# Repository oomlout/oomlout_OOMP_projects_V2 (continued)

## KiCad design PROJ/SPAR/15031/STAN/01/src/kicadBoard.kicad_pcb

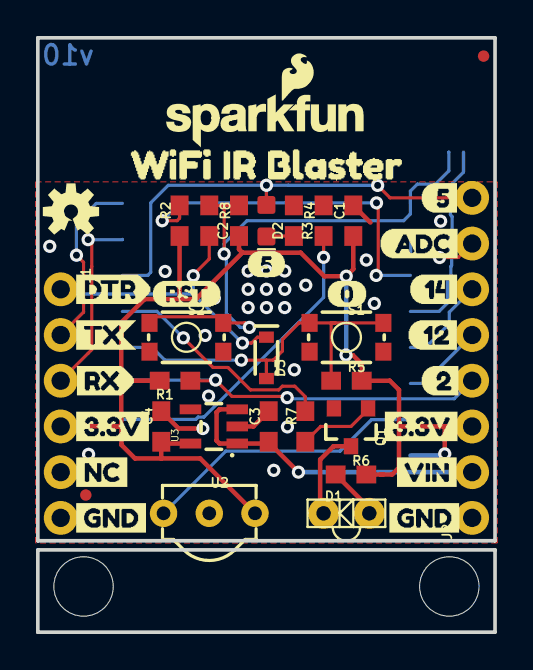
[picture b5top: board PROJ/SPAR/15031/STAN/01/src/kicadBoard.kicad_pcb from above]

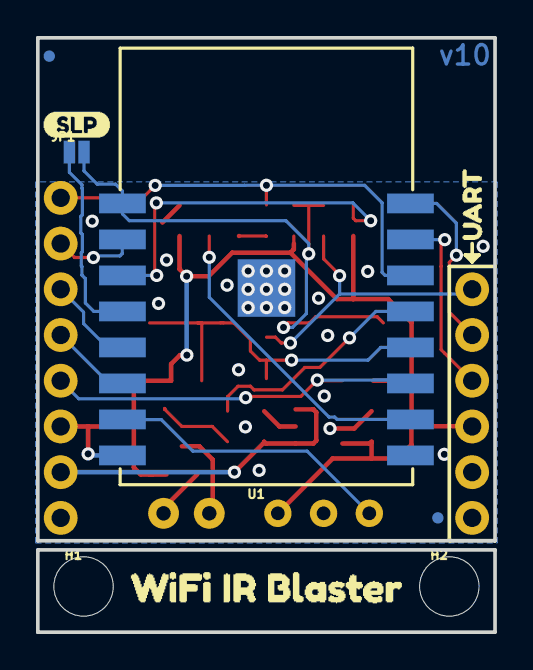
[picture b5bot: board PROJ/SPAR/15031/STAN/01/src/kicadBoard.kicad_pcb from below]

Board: 2 copper layers, 25.4 x 33.0 mm, 55 parts (9 on the bottom side), 22 nets.

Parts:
C1, C2, C3: 1.0uF; 0603
C4: 2.2uF; 0603
D1: IR-LED; LTE-302
D2: GREEN; LED-0603
D3: 250mA/100V; SOD-323
FD1, FD2, FD3, FD4: FIDUCIALUFIDUCIAL; FIDUCIAL-MICRO
FRAME1: FRAME-LETTER; CREATIVE_COMMONS
H1, H2: STAND-OFF
J1: 1X06_NO_SILK
J2: 1X08_NO_SILK
JP1: Deep-Sleep; SMT-JUMPER_2_NO_NO-SILK
LOGO1: OSHW-LOGOS; OSHW-LOGO-S
LOGO2: SFE_LOGO_NAME_FLAME.1_INCH; SFE_LOGO_NAME_FLAME_.1
LOGO3: REVISION
Q1: 600mA/40V; SOT23-3
R1, R2, R4, R8: 10k; 0603
R3, R5, R7: 1k; 0603
R6: 20; 0603
S1: GPIO0; TACTILE_SWITCH_SMD_4.6X2.8MM
S2: RESET; TACTILE_SWITCH_SMD_4.6X2.8MM
U1: ESP-12S
U2: 38kHz; TSOP382
U3: 3.3V; SOT23-5
U$1: 512
U$2, U$21: 3#3V4
U$3: SLP14
U$4, U$13: WIFI_IR_BLASTER11
U$5: UART0
U$6: DTR1
U$7: NC0
U$8: 511
U$9: ADC10
U$10: 129
U$11: 148
U$12: 27
U$14: 013
U$15: RST14
U$19: TX2
U$20: RX3
U$22, U$24: GND5
U$23: VIN6

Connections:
3.3V: C1.1, C4.1, J1.4, J2.3, R1.2, R2.1, R5.2, R6.2, R8.1, U1.8, U2.3, U3.5
ADC: J2.7, U1.2
CHIP_EN: R2.2, U1.3
DTR: C2.2, D3.C, J1.1
GND: C1.2, C3.2, C4.2, J1.6, J2.1, Q1.2, R3.1, R4.2, S1.1, S1.2, S2.1, S2.2, U1.9, U1.P$1, U2.2, U3.2
IO0: D3.A, R5.1, S1.3, S1.4, U1.12
IO2: J2.4, R1.1, U1.11
IO5: D2.A, J2.8, U1.14
IO12: J2.5, U1.6
IO14: J2.6, U1.5
IO15: R4.1, U1.10
IO16: JP1.1, U1.4
IR_IN: U1.7, U2.1
IR_OUT: R7.2, U1.13
unnamed: D2.C, R3.2
unnamed: D1.C, Q1.3
unnamed: D1.A, R6.1
unnamed: Q1.1, R7.1
RESET: C2.1, JP1.2, R8.2, S2.3, S2.4, U1.1
RXI: J1.3, U1.15
TXO: J1.2, U1.16
VIN: C3.1, J2.2, U3.1, U3.3

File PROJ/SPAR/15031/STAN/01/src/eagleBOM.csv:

"Part";"Value";"Device";"Package";"Description";"PROD_ID";"SF_ID";"VALUE";
"C1";"1.0uF";"1.0UF-0603-16V-10%";"0603";"1µF ceramic capacitors";"CAP-00868";"";"1.0uF";
"C2";"1.0uF";"1.0UF-0603-16V-10%";"0603";"1µF ceramic capacitors";"CAP-00868";"";"1.0uF";
"C3";"1.0uF";"1.0UF-0603-16V-10%";"0603";"1µF ceramic capacitors";"CAP-00868";"";"1.0uF";
"C4";"2.2uF";"2.2UF-0603-10V-20%";"0603";"2.2µF ceramic capacitors";"CAP-07888";"";"2.2uF";
"D1";"IR-LED";"LED-IRSIDE_EMITTER";"LTE-302";"Infrared LED (IR)";"DIO-10904";"SEN-00241";"";
"D2";"GREEN";"LED-GREEN0603";"LED-0603";"Green SMD LED";"DIO-00821";"";"GREEN";
"D3";"250mA/100V";"DIODE-BAS16J";"SOD-323";"Diode";"DIO-09646";"";"250mA/100V";
"FD1";"FIDUCIALUFIDUCIAL";"FIDUCIALUFIDUCIAL";"FIDUCIAL-MICRO";"Fiducial Alignment Points";"";"";"";
"FD2";"FIDUCIALUFIDUCIAL";"FIDUCIALUFIDUCIAL";"FIDUCIAL-MICRO";"Fiducial Alignment Points";"";"";"";
"FD3";"FIDUCIALUFIDUCIAL";"FIDUCIALUFIDUCIAL";"FIDUCIAL-MICRO";"Fiducial Alignment Points";"";"";"";
"FD4";"FIDUCIALUFIDUCIAL";"FIDUCIALUFIDUCIAL";"FIDUCIAL-MICRO";"Fiducial Alignment Points";"";"";"";
"FRAME1";"FRAME-LETTER";"FRAME-LETTER";"CREATIVE_COMMONS";"Schematic Frame - Letter";"";"";"";
"H1";"STAND-OFF";"STAND-OFF";"STAND-OFF";"Stand Off";"";"";"";
"H2";"STAND-OFF";"STAND-OFF";"STAND-OFF";"Stand Off";"";"";"";
"J1";"";"6_PIN_SERIAL_TARGETNO_SILK";"1X06_NO_SILK";"6-pin header connection for use with the "FTDI BASIC" pinout - TARGET SIDE.";"";"";"";
"J2";"";"CONN_08NO_SILK_FEMALE_PTH";"1X08_NO_SILK";"Multi connection point. Often used as Generic Header-pin footprint for 0.1 inch spaced/style header connections";"CONN-08438";"";"";
"JP1";"Deep-Sleep";"JUMPER-SMT_2_NO_NO-SILK";"SMT-JUMPER_2_NO_NO-SILK";"Normally open jumper";"";"";"";
"LOGO1";"OSHW-LOGOS";"OSHW-LOGOS";"OSHW-LOGO-S";"Open-Source Hardware (OSHW) Logo";"";"";"";
"LOGO2";"SFE_LOGO_NAME_FLAME.1_INCH";"SFE_LOGO_NAME_FLAME.1_INCH";"SFE_LOGO_NAME_FLAME_.1";"SparkFun Font Logo w/ Flame";"";"";"";
"LOGO3";"REVISION";"REVISION";"REVISION";""Revision By" Text";"";"";"";
"Q1";"600mA/40V";"TRANS_NPN-MMBT2222AL";"SOT23-3";"NPN transistor";"TRANS-08049";"";"600mA/40V";
"R1";"10k";"10KOHM-0603-1/10W-1%";"0603";"10kΩ resistor";"RES-00824";"";"10k";
"R2";"10k";"10KOHM-0603-1/10W-1%";"0603";"10kΩ resistor";"RES-00824";"";"10k";
"R3";"1k";"1KOHM-0603-1/10W-1%";"0603";"1kΩ resistor";"RES-07856";"";"1k";
"R4";"10k";"10KOHM-0603-1/10W-1%";"0603";"10kΩ resistor";"RES-00824";"";"10k";
"R5";"1k";"1KOHM-0603-1/10W-1%";"0603";"1kΩ resistor";"RES-07856";"";"1k";
"R6";"20";"20OHM-0603-1/10W-1%";"0603";"RES-07862";"RES-07862";"";"20";
"R7";"1k";"1KOHM-0603-1/10W-1%";"0603";"1kΩ resistor";"RES-07856";"";"1k";
"R8";"10k";"10KOHM-0603-1/10W-1%";"0603";"10kΩ resistor";"RES-00824";"";"10k";
"S1";"GPIO0";"MOMENTARY-SWITCH-SPST-SMD-4.6X2.8MM";"TACTILE_SWITCH_SMD_4.6X2.8MM";"Momentary Switch (Pushbutton) - SPST";"SWCH-13065";"";"";
"S2";"RESET";"MOMENTARY-SWITCH-SPST-SMD-4.6X2.8MM";"TACTILE_SWITCH_SMD_4.6X2.8MM";"Momentary Switch (Pushbutton) - SPST";"SWCH-13065";"";"";
"U1";"ESP-12S";"ESP-12S";"ESP-12S";"AI-Thinker ESP-12S";"IC-14115";"";"";
"U2";"38kHz";"TSOP38238";"TSOP382";"Vishay Semiconductor TSOP32838 - 38kHz IR Receiver";"SEN-14114";"";"38kHz";
"U3";"3.3V";"V_REG_AP2112K-3.3V";"SOT23-5";"AP2112 - 600mA CMOS LDO Regulator w/ Enable";"VREG-12457";"";"3.3V";

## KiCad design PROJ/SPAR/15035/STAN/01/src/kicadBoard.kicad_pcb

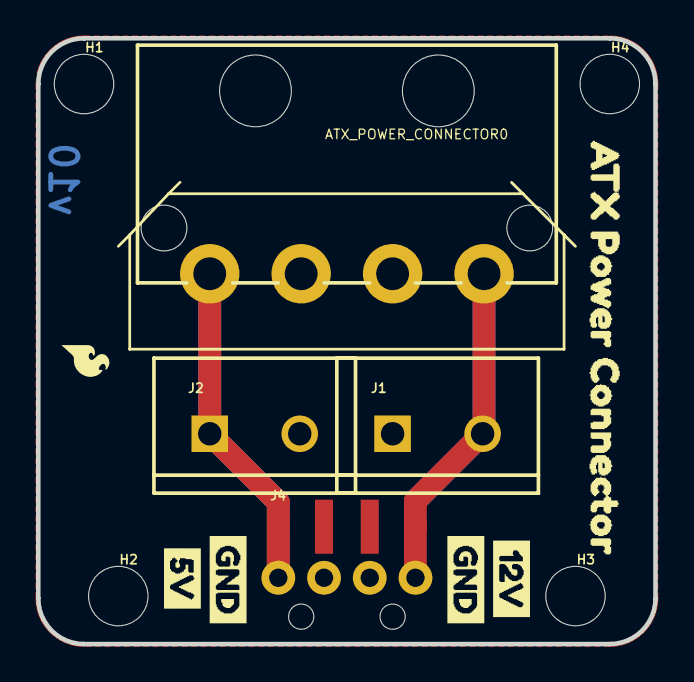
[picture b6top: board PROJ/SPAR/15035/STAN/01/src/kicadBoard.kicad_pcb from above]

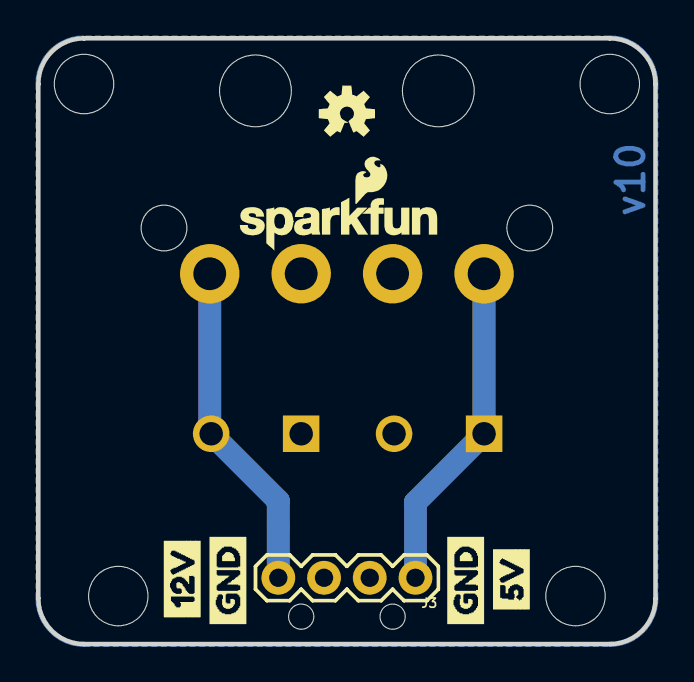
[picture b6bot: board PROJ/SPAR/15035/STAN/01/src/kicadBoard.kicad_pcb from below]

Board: 2 copper layers, 34.3 x 33.7 mm, 22 parts (7 on the bottom side), 3 nets.

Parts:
ATX_POWER_CONNECTOR0: COMPUTER_PERIPHERAL_POWERRA-VT; COMPUTER-PERIPHERAL-POWER-RA-VT
FRAME1: FRAME-LETTER; CREATIVE_COMMONS
H1, H2, H3, H4: STAND-OFF
J1, J2: SCREWTERMINAL-5MM-2
J3: 1X04
J4: 1X04_SMD_RA_MALE
LOGO1: OSHW-LOGOS; OSHW-LOGO-S
LOGO2: SFE_LOGO_NAME_FLAME.1_INCH; SFE_LOGO_NAME_FLAME_.1
LOGO3: SFE_LOGO_FLAME.1_INCH; SFE_LOGO_FLAME_.1
U$1, U$5: 12V0
U$2, U$8: 5V0
U$3, U$4, U$6, U$7: GND0
U$9: ATX_POWER_CONNECTOR0

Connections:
5V: ATX_POWER_CONNECTOR0.5V, J2.1, J3.1, J4.1
12V: ATX_POWER_CONNECTOR0.12V, J1.2, J3.4, J4.4
GND: ATX_POWER_CONNECTOR0.GND@1, ATX_POWER_CONNECTOR0.GND@2, J1.1, J2.2, J3.2, J3.3, J4.2, J4.3

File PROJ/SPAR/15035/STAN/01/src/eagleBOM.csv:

"Part";"Value";"Device";"Package";"Description";"PROD_ID";"SF_ID";"SF_SKU";
"ATX_POWER_CONNECTOR";"COMPUTER_PERIPHERAL_POWERRA-VT";"COMPUTER_PERIPHERAL_POWERRA-VT";"COMPUTER-PERIPHERAL-POWER-RA-VT";"ATX 4-Pin Power Supply Connector - Right Angle and Vertical PTH Mount";"PRT-15700";"";"";
"FRAME1";"FRAME-LETTER";"FRAME-LETTER";"CREATIVE_COMMONS";"Schematic Frame - Letter";"";"";"";
"H1";"STAND-OFF";"STAND-OFF";"STAND-OFF";"Stand Off";"";"";"";
"H2";"STAND-OFF";"STAND-OFF";"STAND-OFF";"Stand Off";"";"";"";
"H3";"STAND-OFF";"STAND-OFF";"STAND-OFF";"Stand Off";"";"";"";
"H4";"STAND-OFF";"STAND-OFF";"STAND-OFF";"Stand Off";"";"";"";
"J1";"";"CONN_025MM";"SCREWTERMINAL-5MM-2";"Multi connection point. Often used as Generic Header-pin footprint for 0.1 inch spaced/style header connections";"";"";"PRT-08432";
"J2";"";"CONN_025MM";"SCREWTERMINAL-5MM-2";"Multi connection point. Often used as Generic Header-pin footprint for 0.1 inch spaced/style header connections";"";"";"PRT-08432";
"J3";"";"CONN_04";"1X04";"Multi connection point. Often used as Generic Header-pin footprint for 0.1 inch spaced/style header connections";"CONN-09696";"";"";
"J4";"";"CONN_04SMD";"1X04_SMD_RA_MALE";"Multi connection point. Often used as Generic Header-pin footprint for 0.1 inch spaced/style header connections";"CONN-09140";"PRT-12638";"";
"LOGO1";"OSHW-LOGOS";"OSHW-LOGOS";"OSHW-LOGO-S";"Open-Source Hardware (OSHW) Logo";"";"";"";
"LOGO2";"SFE_LOGO_NAME_FLAME.1_INCH";"SFE_LOGO_NAME_FLAME.1_INCH";"SFE_LOGO_NAME_FLAME_.1";"SparkFun Font Logo w/ Flame";"";"";"";
"LOGO3";"SFE_LOGO_FLAME.1_INCH";"SFE_LOGO_FLAME.1_INCH";"SFE_LOGO_FLAME_.1";"SparkFun Flame Logo";"";"";"";

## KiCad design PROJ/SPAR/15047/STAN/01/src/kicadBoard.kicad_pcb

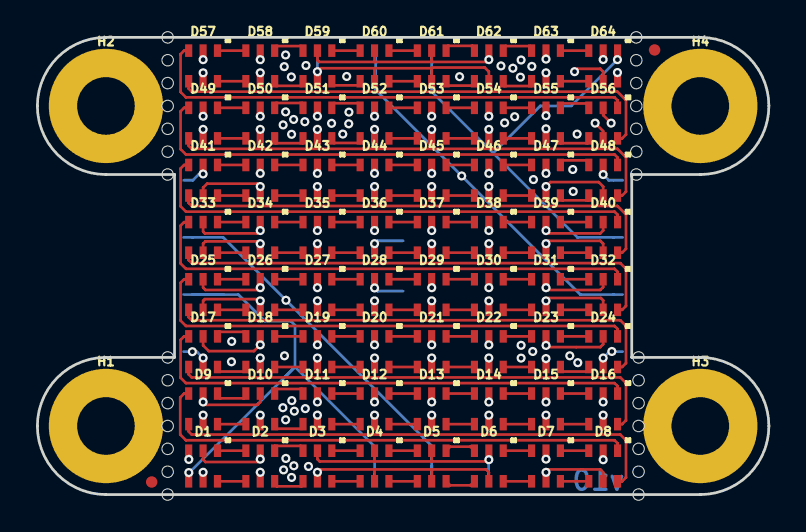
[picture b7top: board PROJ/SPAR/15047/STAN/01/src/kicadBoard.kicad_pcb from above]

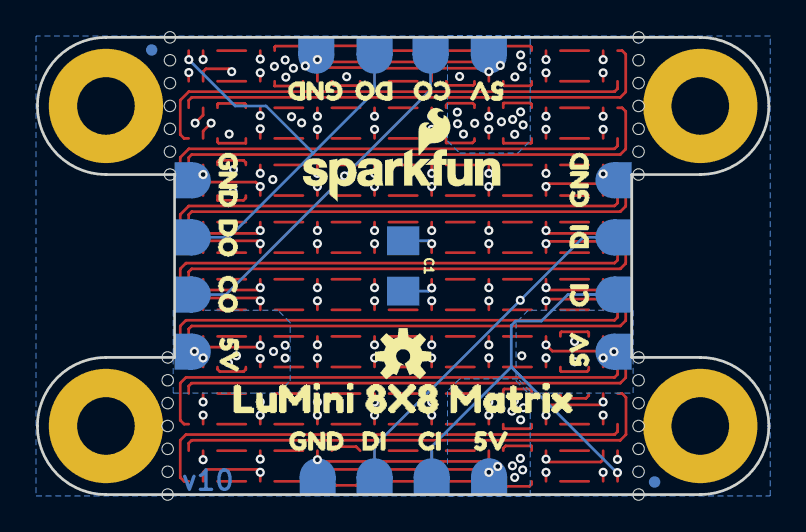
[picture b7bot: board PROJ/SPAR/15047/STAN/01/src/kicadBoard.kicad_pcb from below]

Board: 4 copper layers, 40.6 x 25.4 mm, 138 parts (38 on the bottom side), 132 nets.

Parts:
@HOLE0, @HOLE1, @HOLE2, @HOLE3, @HOLE4, @HOLE5, @HOLE6, @HOLE7, @HOLE8, @HOLE9, @HOLE10, @HOLE11, @HOLE12, @HOLE13, @HOLE14, @HOLE15, @HOLE16, @HOLE17, @HOLE18, @HOLE19, @HOLE20, @HOLE21, @HOLE22, @HOLE23, @HOLE24, @HOLE25, @HOLE26, @HOLE27: (no value)
C1: DNP; 1206
D1, D2, D3, D4, D5, D6, D7, D8, D9, D10, D11, D12, D13, D14, D15, D16, D17, D18, D19, D20, D21, D22, D23, D24, D25, D26, D27, D28, D29, D30, D31, D32, D33, D34, D35, D36, D37, D38, D39, D40, D41, D42, D43, D44, D45, D46, D47, D48, D49, D50, D51, D52, D53, D54, D55, D56, D57, D58, D59, D60, D61, D62, D63, D64: APA102-2020
FD1, FD2, FD3, FD4: FIDUCIALUFIDUCIAL; FIDUCIAL-MICRO
FRAME1: FRAME-LEDGER; CREATIVE_COMMONS
H1, H2, H3, H4: STANDOFF_ELECTRICAL-NOTHERMALS; STANDOFF-ELECTRICAL-NOTHERMALS
J1, J2, J3, J4, J5, J6, J7, J8, J9, J10, J11, J12, J13, J14, J15, J16: LED_PAD; CIRCULARPAD
LOGO1: SFE_LOGO_NAME_FLAME.1_INCH; SFE_LOGO_NAME_FLAME_.1
LOGO2: OSHW-LOGOS; OSHW-LOGO-S
U$1, U$2, U$11, U$18: 5V5
U$3, U$12: CI1
U$4, U$17: CO3
U$5, U$13: DI2
U$6, U$16: DO4
U$7, U$8, U$14, U$15: GND6
U$9: LUMINI_8X8_MATRIX0
U$10: ORDERING_INSTRUCTIONS

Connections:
5V: C1.1, D1.VDD, D2.VDD, D3.VDD, D4.VDD, D5.VDD, D6.VDD, D7.VDD, D8.VDD, D9.VDD, D10.VDD, D11.VDD, D12.VDD, D13.VDD, D14.VDD, D15.VDD, D16.VDD, D17.VDD, D18.VDD, D19.VDD, D20.VDD, D21.VDD, D22.VDD, D23.VDD, D24.VDD, D25.VDD, D26.VDD, D27.VDD, D28.VDD, D29.VDD, D30.VDD, D31.VDD, D32.VDD, D33.VDD, D34.VDD, D35.VDD, D36.VDD, D37.VDD, D38.VDD, D39.VDD, D40.VDD, D41.VDD, D42.VDD, D43.VDD, D44.VDD, D45.VDD, D46.VDD, D47.VDD, D48.VDD, D49.VDD, D50.VDD, D51.VDD, D52.VDD, D53.VDD, D54.VDD, D55.VDD, D56.VDD, D57.VDD, D58.VDD, D59.VDD, D60.VDD, D61.VDD, D62.VDD, D63.VDD, D64.VDD, J1.P$1, J1.P$2, J2.P$1, J2.P$2, J5.P$1, J5.P$2, J8.P$1, J8.P$2
CI: D1.CKI, J9.P$1, J9.P$2, J10.P$1, J10.P$2
CO: D64.CKO, J13.P$1, J13.P$2, J14.P$1, J14.P$2
CT1: D9.CKO, D10.CKI
CT2: D18.CKO, D19.CKI
CT3: D27.CKO, D28.CKI
CT4: D36.CKO, D37.CKI
CT5: D45.CKO, D46.CKI
CT6: D54.CKO, D55.CKI
CT7: D63.CKO, D64.CKI
DI: D1.SDI, J11.P$1, J11.P$2, J12.P$1, J12.P$2
DO: D64.SDO, J15.P$1, J15.P$2, J16.P$1, J16.P$2
DT1: D9.SDO, D10.SDI
DT2: D18.SDO, D19.SDI
DT3: D27.SDO, D28.SDI
DT4: D36.SDO, D37.SDI
DT5: D45.SDO, D46.SDI
DT6: D54.SDO, D55.SDI
DT7: D63.SDO, D64.SDI
GND: C1.2, D1.GND, D2.GND, D3.GND, D4.GND, D5.GND, D6.GND, D7.GND, D8.GND, D9.GND, D10.GND, D11.GND, D12.GND, D13.GND, D14.GND, D15.GND, D16.GND, D17.GND, D18.GND, D19.GND, D20.GND, D21.GND, D22.GND, D23.GND, D24.GND, D25.GND, D26.GND, D27.GND, D28.GND, D29.GND, D30.GND, D31.GND, D32.GND, D33.GND, D34.GND, D35.GND, D36.GND, D37.GND, D38.GND, D39.GND, D40.GND, D41.GND, D42.GND, D43.GND, D44.GND, D45.GND, D46.GND, D47.GND, D48.GND, D49.GND, D50.GND, D51.GND, D52.GND, D53.GND, D54.GND, D55.GND, D56.GND, D57.GND, D58.GND, D59.GND, D60.GND, D61.GND, D62.GND, D63.GND, D64.GND, H1.P1, H2.P1, H3.P1, H4.P1, J3.P$1, J3.P$2, J4.P$1, J4.P$2, J6.P$1, J6.P$2, J7.P$1, J7.P$2
unnamed: D1.SDO, D2.SDI
unnamed: D1.CKO, D2.CKI
unnamed: D2.SDO, D3.SDI
unnamed: D2.CKO, D3.CKI
unnamed: D3.SDO, D4.SDI
unnamed: D3.CKO, D4.CKI
unnamed: D4.SDO, D5.SDI
unnamed: D4.CKO, D5.CKI
unnamed: D5.SDO, D6.SDI
unnamed: D5.CKO, D6.CKI
unnamed: D6.SDO, D7.SDI
unnamed: D6.CKO, D7.CKI
unnamed: D7.SDO, D8.SDI
unnamed: D7.CKO, D8.CKI
unnamed: D8.SDO, D9.SDI
unnamed: D8.CKO, D9.CKI
unnamed: D10.SDO, D11.SDI
unnamed: D10.CKO, D11.CKI
unnamed: D11.SDO, D12.SDI
unnamed: D11.CKO, D12.CKI
unnamed: D12.SDO, D13.SDI
unnamed: D12.CKO, D13.CKI
unnamed: D13.SDO, D14.SDI
unnamed: D13.CKO, D14.CKI
unnamed: D14.SDO, D15.SDI
unnamed: D14.CKO, D15.CKI
unnamed: D15.SDO, D16.SDI
unnamed: D15.CKO, D16.CKI
unnamed: D16.SDO, D17.SDI
unnamed: D16.CKO, D17.CKI
unnamed: D17.SDO, D18.SDI
unnamed: D17.CKO, D18.CKI
unnamed: D19.SDO, D20.SDI
unnamed: D19.CKO, D20.CKI
unnamed: D20.SDO, D21.SDI
unnamed: D20.CKO, D21.CKI
unnamed: D21.SDO, D22.SDI
unnamed: D21.CKO, D22.CKI
unnamed: D22.SDO, D23.SDI
unnamed: D22.CKO, D23.CKI
unnamed: D23.SDO, D24.SDI
unnamed: D23.CKO, D24.CKI
unnamed: D24.SDO, D25.SDI
unnamed: D24.CKO, D25.CKI
unnamed: D25.SDO, D26.SDI
unnamed: D25.CKO, D26.CKI
unnamed: D26.SDO, D27.SDI
unnamed: D26.CKO, D27.CKI
unnamed: D28.SDO, D29.SDI
unnamed: D28.CKO, D29.CKI
unnamed: D29.SDO, D30.SDI
unnamed: D29.CKO, D30.CKI
unnamed: D30.SDO, D31.SDI
unnamed: D30.CKO, D31.CKI
unnamed: D31.SDO, D32.SDI
unnamed: D31.CKO, D32.CKI
unnamed: D32.SDO, D33.SDI
unnamed: D32.CKO, D33.CKI
unnamed: D33.SDO, D34.SDI
unnamed: D33.CKO, D34.CKI
unnamed: D34.SDO, D35.SDI
unnamed: D34.CKO, D35.CKI
unnamed: D35.SDO, D36.SDI
unnamed: D35.CKO, D36.CKI
unnamed: D37.SDO, D38.SDI
unnamed: D37.CKO, D38.CKI
unnamed: D38.SDO, D39.SDI
unnamed: D38.CKO, D39.CKI
unnamed: D39.SDO, D40.SDI
unnamed: D39.CKO, D40.CKI
unnamed: D40.SDO, D41.SDI
unnamed: D40.CKO, D41.CKI
unnamed: D41.SDO, D42.SDI
unnamed: D41.CKO, D42.CKI
unnamed: D42.SDO, D43.SDI
unnamed: D42.CKO, D43.CKI
unnamed: D43.SDO, D44.SDI
unnamed: D43.CKO, D44.CKI
unnamed: D44.SDO, D45.SDI
unnamed: D44.CKO, D45.CKI
unnamed: D46.SDO, D47.SDI
unnamed: D46.CKO, D47.CKI
unnamed: D47.SDO, D48.SDI
unnamed: D47.CKO, D48.CKI
unnamed: D48.SDO, D49.SDI
unnamed: D48.CKO, D49.CKI
unnamed: D49.SDO, D50.SDI
unnamed: D49.CKO, D50.CKI
unnamed: D50.SDO, D51.SDI
unnamed: D50.CKO, D51.CKI
unnamed: D51.SDO, D52.SDI
unnamed: D51.CKO, D52.CKI
unnamed: D52.SDO, D53.SDI
unnamed: D52.CKO, D53.CKI
unnamed: D53.SDO, D54.SDI
unnamed: D53.CKO, D54.CKI
unnamed: D55.SDO, D56.SDI
unnamed: D55.CKO, D56.CKI
unnamed: D56.SDO, D57.SDI
unnamed: D56.CKO, D57.CKI
unnamed: D57.SDO, D58.SDI
unnamed: D57.CKO, D58.CKI
unnamed: D58.SDO, D59.SDI
unnamed: D58.CKO, D59.CKI
unnamed: D59.SDO, D60.SDI
unnamed: D59.CKO, D60.CKI
unnamed: D60.SDO, D61.SDI
unnamed: D60.CKO, D61.CKI
unnamed: D61.SDO, D62.SDI
unnamed: D61.CKO, D62.CKI
unnamed: D62.SDO, D63.SDI
unnamed: D62.CKO, D63.CKI

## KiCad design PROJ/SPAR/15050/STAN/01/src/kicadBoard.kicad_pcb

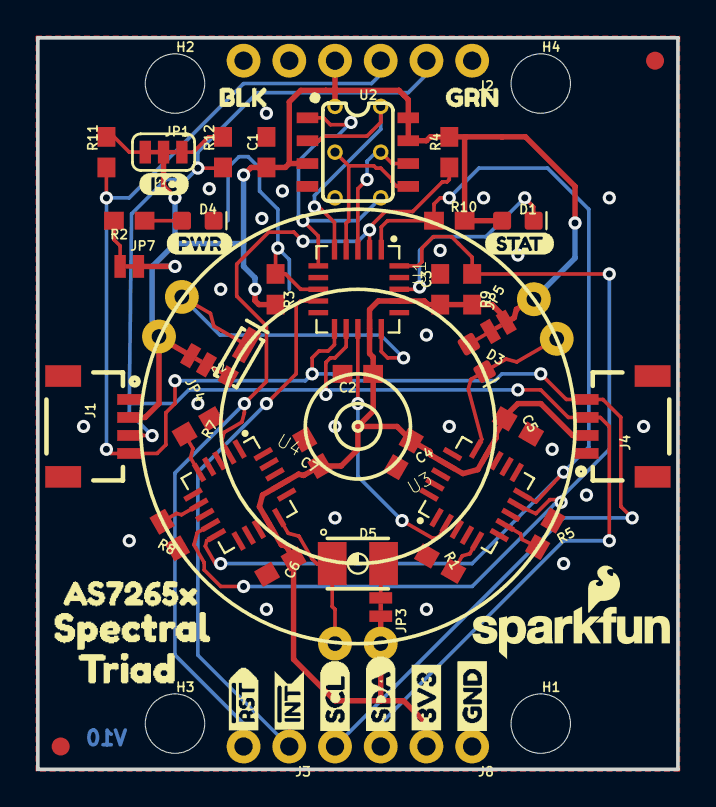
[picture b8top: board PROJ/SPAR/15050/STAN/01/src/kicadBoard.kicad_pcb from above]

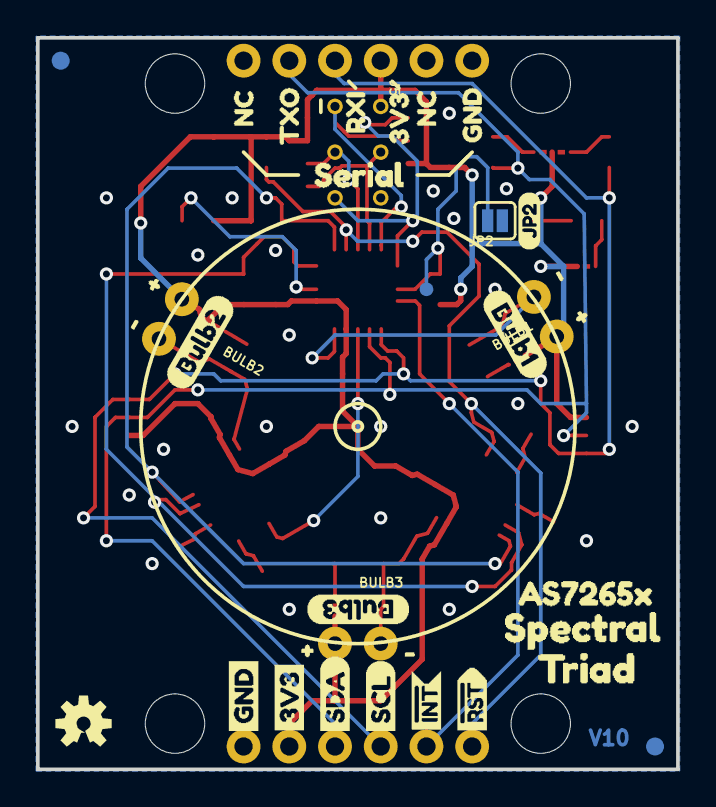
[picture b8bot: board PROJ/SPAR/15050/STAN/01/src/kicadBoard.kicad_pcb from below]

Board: 2 copper layers, 35.6 x 40.6 mm, 95 parts (35 on the bottom side), 29 nets.

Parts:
BULB1, BULB2, BULB3: LED_5MM_NOSILK
C1: 1.0uF; 0603
C2, C4, C6: 0.1uF; 0603
C3, C5, C7: 10uF; 0603
D1: BLUE; LED-0603
D2: 5700k; SUPER_BRIGHT_SMD_LED_3014
D3: IR; LED-0603
D4: RED; LED-0603
D5: UV; PLCC-2
FD1, FD2, FD3, FD4: FIDUCIAL1X2; FIDUCIAL-1X2
FRAME1, FRAME3: FRAME-LETTER; CREATIVE_COMMONS
H1, H2, H3, H4: STAND-OFF
J1, J4: 1X04_1MM_RA
J2: Serial Interface; 1X06_NO_SILK
J3: 1X02_NO_SILK
J5: Flash Programming; 2X3_TEST_POINTS
J8: PTH; 1X04_NO_SILK
JP1: SMT-JUMPER_3_2-NC_TRACE_SILK
JP2: SMT-JUMPER_2_NO_SILK
JP3, JP4, JP5, JP7: SMT-JUMPER_2_NC_TRACE_NO-SILK
LOGO1: SFE_LOGO_NAME_FLAME.1_INCH; SFE_LOGO_NAME_FLAME_.1
LOGO4: OSHW-LOGOS; OSHW-LOGO-S
R1, R3, R4, R5, R7, R8: 10k; 0603
R2: 1k; 0603
R9, R10, R11, R12: 2.2k; 0603
TP1: PAD.03X.03
U1: AS72651; LGA20
U2: 4MB Flash; SO08
U3: AS72652; LGA20
U4: AS72653; LGA20
U$1, U$36, U$37: #0
U$2: I_SUPER2_C-()-03
U$3: PWR-()-03
U$4, U$14: AS7265X0
U$5: BULB15
U$6: BULB26
U$7: BULB37
U$8: JP20
U$9, U$13: SPECTRAL1
U$10: STAT4
U$11, U$12: TRIAD2
U$15: 3V33
U$16: BLK7
U$17: GND5
U$18: GRN6
U$19, U$20: NC4
U$21: RXI2
U$22: SERIAL0
U$23: TXO1
U$24, U$31: 3V3-04
U$25, U$30: GND-04
U$26, U$32: SDA-[)
U$27, U$33: SCL-[)
U$28, U$34: INT#-[_-04
U$29, U$35: RST#-[_-04
U$38, U$39, U$40: #1

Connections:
3.3V: BULB1.A, BULB2.A, BULB3.A, C1.1, C2.1, C3.1, C4.1, C5.1, C6.1, C7.1, D1.A, J1.2, J2.4, J4.2, J5.2, J8.2, JP1.2, JP3.2, JP4.2, JP5.2, JP7.2, R3.2, R4.2, R9.2, R10.2, U1.14, U1.17, U2.3, U2.7, U2.8, U3.14, U3.17, U4.14, U4.17
GND: C1.2, C2.2, C3.2, C4.2, C5.2, C6.2, C7.2, D4.C, J1.1, J2.6, J4.1, J5.6, J8.1, JP2.1, R1.1, R5.1, R7.1, R8.1, U1.16, U2.4, U3.16, U4.16
I2C_ENB: JP2.2, R3.1, TP1.P$1, U1.8
LED_DRV: BULB1.K, D2.C, U1.15
LED_DRV1: BULB2.K, D3.C, U3.15
LED_DRV2: BULB3.K, D5.C, U4.15
MISO: J5.1, U1.5, U2.2
MOSI: J5.4, U1.4, U2.5
unnamed: JP7.1, R2.2
unnamed: D1.C, U1.18
unnamed: R5.2, U3.7
unnamed: JP1.3, R12.2
unnamed: JP1.1, R11.2
unnamed: D2.A, JP4.1
unnamed: D4.A, R2.1
unnamed: D3.A, JP5.1
unnamed: R1.2, U3.5
unnamed: D5.A, JP3.1
unnamed: R8.2, U4.7
unnamed: R7.2, U4.5
RX/SCL: J1.4, J2.3, J4.4, J8.4, R11.1, U1.11
SCK: J5.3, U1.3, U2.6
SCL_S: R9.1, U1.20, U3.9, U4.9
SDA_S: R10.1, U1.1, U3.10, U4.10
TX/SDA: J1.3, J2.2, J4.3, J8.3, R12.1, U1.12
~CS_EE: J5.5, U1.6, U2.1
~INT: J3.1, U1.9
~RST-ADDR: U1.13, U3.2
~RST: J3.2, R4.1, U1.2, U4.2
